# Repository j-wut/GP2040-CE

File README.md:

<p align="center">
  
</p>

<p align="center">
  Multi-Platform Gamepad Firmware for RP2040
</p>

<p align="center">

  <br />

</p>

<p>
  GP2040-CE (Community Edition) is a gamepad firmware for the Raspberry Pi Pico and other boards based on the RP2040 microcontrollers that combines multi-platform compatibility, low latency and a rich feature set to provide endless customization possibilities without sacrificing performance.
</p>

<p>
  GP2040-CE is compatible with PC, PS3, PS4, PS5, Nintendo Switch, Xbox One, Steam Deck, MiSTer and Android.
</p>

## Links

[Downloads](https://gp2040-ce.info/downloads) | [Installation](https://gp2040-ce.info/installation) | [Wiring](https://gp2040-ce.info/controller-build/wiring) | [Usage](https://gp2040-ce.info/usage) | [FAQ](https://gp2040-ce.info/faq/faq-general) | [GitHub](https://github.com/OpenStickCommunity/GP2040-CE)

Full documentation can be found at [https://gp2040-ce.info](https://gp2040-ce.info)

## Features

- Select from 14 input modes including X-Input, Nintendo Switch, Playstation 4/5, Xbox One, D-Input, and Keyboard
- Input latency average of 0.76ms in Xinput and 0.91ms for Playstation 5.
- Multiple SOCD cleaning modes - Up Priority (a.k.a. Stickless), Neutral, and Second Input Priority.
- Left and Right stick emulation via D-pad inputs as well as dedicated toggle switches.
- Dual direction via D-pad + LS/RS.
- Reversed input via a button.
- [Turbo and Turbo LED](https://gp2040-ce.info/add-ons/turbo) with selectable speed
- Per-button RGB LED support.
- PWM Player indicator LED support (XInput only).
- Multiple LED profiles support.
- Support for 128x64 monochrome I2C displays - SSD1306, SH1106, and SH1107 compatible.
- Custom startup splash screen and easy image upload via web configuration.
- Support for passive buzzer speaker (3v or 5v).
- [Built-in, embedded web configuration](https://gp2040-ce.info/web-configurator) - No download required!

Visit the [GP2040-CE Usage](https://gp2040-ce.info/usage) page for more details.

## Performance

Input latency is tested using the methodology outlined at [WydD's inputlag.science website](https://inputlag.science/controller/methodology), using the default 1000 Hz (1 ms) polling rate in the firmware. You can read more about the setup we use to conduct latency testing [HERE](https://github.com/OpenStickCommunity/Site/blob/main/latency_testing/README.md) if you are interested in testing for yourself or would just like to know more about the devices used to do the testing.

| Version | Mode    | Poll Rate | Min     | Max     | Avg     | Stdev   | % on time | %1f skip | %2f skip |
| ------- | ------- | --------- | ------- | ------- | ------- | ------- | --------- | -------- | -------- |
| v0.7.12 | Xinput  | 1 ms      | 0.45 ms | 1.28 ms | 0.76 ms | 0.24 ms | 98.48%    | 1.52%    | 0%       |
| v0.7.12 | Switch  | 1 ms      | 0.41 ms | 1.22 ms | 0.72 ms | 0.24 ms | 98.53%    | 1.47%    | 0%       |
| v0.7.12 | HID USB | 1 ms      | 0.42 ms | 1.25 ms | 0.73 ms | 0.24 ms | 98.52%    | 1.48%    | 0%       |
| v0.7.12 | PS3     | 1 ms      | 0.52 ms | 1.46 ms | 0.83 ms | 0.24 ms | 98.37%    | 1.63%    | 0%       |
| v0.7.12 | PS4     | 1 ms      | 0.55 ms | 2.33 ms | 0.90 ms | 0.32 ms | 98.19%    | 1.81%    | 0%       |
| v0.7.12 | PS5     | 1 ms      | 0.55 ms | 2.38 ms | 0.91 ms | 0.32 ms | 98.18%    | 1.82%    | 0%       |

Full results can be found in the [GP2040-CE v0.7.12 Firmware Latency Test Results](https://github.com/OpenStickCommunity/Site/raw/main/latency_testing/GP2040-CE_Firmware_Latency_Test_Results_v0.7.12.xlsx) .xlsx Sheet.

Results from v0.7.11 can be found [HERE](https://github.com/OpenStickCommunity/Site/raw/main/latency_testing/GP2040-CE_Firmware_Latency_Test_Results_v0.7.11.xlsx). Previous results can be found in the `latency_testing` folder.

### Raspberry Pi 5 / CM5 / Pi 4 / CM4 (Linux USB gadget)

The [`linux/`](linux/README.md) folder has a separate GP2040-CE build that runs on a Raspberry Pi under Linux and acts as a USB controller through the Pi's USB device port. These boards have High Speed USB, so they can ask the host for polling up to 8 kHz. RP2040 and RP2350 boards are Full Speed only and stay at the 1 kHz maximum.

## Support

If you would like to discuss features, issues or anything else related to GP2040-CE please [create an issue](https://github.com/OpenStickCommunity/GP2040-CE/issues/new) or join the [OpenStick GP2040-CE Discord](https://discord.gg/k2pxhke7q8) support channel.

## Contributing

Want to help improve GP2040-CE? There are a bunch of ways to contribute!

### Community Participation

Have an idea for a cool new feature, or just want to discuss some technical details with the developers? Join the [OpenStick GP2040-CE Discord](https://discord.gg/k2pxhke7q8) server to participate in our active and ever-growing community!

### Pull Requests

Pull requests are welcome and encouraged for enhancements, bug fixes and documentation updates.

Please respect the coding style of the file(s) you are working in, and enforce the use of the `.editorconfig` file when present.

## Acknowledgements

- [FeralAI](https://github.com/FeralAI) for building [GP2040](https://github.com/FeralAI/GP2040) and laying the foundation for this community project
- Ha Thach's excellent [TinyUSB library](https://github.com/hathach/tinyusb) examples
- fluffymadness's [tinyusb-xinput](https://github.com/fluffymadness/tinyusb-xinput) sample
- Kevin Boone's [blog post on using RP2040 flash memory as emulated EEPROM](https://kevinboone.me/picoflash.html)
- [bitbank2](https://github.com/bitbank2) for the [OneBitDisplay](https://github.com/bitbank2/OneBitDisplay) and [BitBang_I2C](https://github.com/bitbank2/BitBang_I2C) libraries, which were ported for use with the Pico SDK
- [arntsonl](https://github.com/arntsonl) for the amazing cleanup and feature additions that brought us to v0.5.0
- [alirin222](https://github.com/alirin222) for the awesome turbo code ([@alirin222](https://twitter.com/alirin222) on Twitter)
- [deeebug](https://github.com/deeebug) for improvements to the web-UI and fixing the PS3 home button issue
- [TheTrain](https://github.com/TheTrainGoes/GP2040-Projects) and [Fortinbra](https://github.com/Fortinbra) for helping keep our community chugging along
- [PassingLink](https://github.com/passinglink/passinglink) for the technical details and code for PS4 implementation
- [Youssef Habchi](https://youssef-habchi.com/) for allowing us to purchase a license to use Road Rage font for the project
- [tamanegitaro](https://github.com/tamanegitaro/) and [alirin222](https://github.com/alirin222) for the basis of the mini/classic controller work
- [Ryzee119](https://github.com/Ryzee119) for the wonderful [ogx360_t4](https://github.com/Ryzee119/ogx360_t4/) and xid_driver library for Original Xbox support
- [Santroller](https://github.com/Santroller/Santroller) and [GIMX](https://github.com/matlo/GIMX) for technical examples of Xbox One authentication using pass-through
- [Santroller](https://github.com/Santroller/Santroller) for the code necessary to have Xbox 360 run without a dongle
- [Dycool](https://github.com/Dycool)'s [NS-PC-Control](https://github.com/Dycool/NS-PC-Control) for the technical details on wired Joy-Con, NES and Famicom controller identities
- [PVS-Studio](https://pvs-studio.com/en/pvs-studio/?utm_source=website&utm_medium=github&utm_campaign=open_source) for static code analysis

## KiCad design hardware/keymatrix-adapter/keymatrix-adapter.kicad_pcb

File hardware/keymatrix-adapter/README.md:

# Key matrix diode adapter

A board that turns the 20-pin header of the **RP2040 Advanced Breakout Board (USB Passthrough edition)** into 44
matrix switch inputs with full N-key rollover: all 15 button pins as 4 rows x 11 columns. It goes with the
[RP2040AdvancedBreakoutBoardUSBPassthroughMatrix](../../configs/RP2040AdvancedBreakoutBoardUSBPassthroughMatrix)
firmware config.

- 156 x 112 mm, 2 layers, all through-hole connectors plus 44 SOD-123 diodes.
- **J1** connects to the breakout board's 20-pin header with a straight 20-pin IDC ribbon cable (pin 1 to pin 1).
- **J2-J5** are two pairs of 20-pin switch connectors (A and B).
- **J6-J14** are screw terminals: two per switch, in the same order as the connector pins. The last 4 switches
  are on screw terminals only.
- One 1N4148W diode per switch, already on the board. No diodes are needed in the wiring.

## How a switch is wired

Every switch has a **slot** with two contacts, A and B. Wire the switch between them, either on the connector pair
(pin N on A and pin N on B) or on its two neighbouring screw terminals. Both reach the same switch. A switch has no
polarity, so either wire can go to A.

- **A** goes through the switch's diode to its row.
- **B** is its column. All the B contacts of one column are connected on the board, so a harness can share them.
  A contacts must never be shared.

Do not plug a normal 20-pin button harness (buttons wired to ground) into the switch connectors.

## Slot order

Both pairs have the same order. **Pair 1 follows the breakout's 20-pin header.** Each of its 15 button pins
carries the switch that defaults to that pin's button, so a harness made for the breakout's pinout lines up:

- Pin 16 is K4 (L2), pin 8 is P1 (B3), pin 1 is U (Up), and so on.

The breakout's 5 power and ground positions (pins 12 and 17-20) carry five more switches. Pair 2 carries the next
20 in row order, and the last 4 are on screw terminals only. R*n*C*m* is the switch in row *n*, column *m*, as listed in the web config (Add-ons > Keyboard
Matrix).

| Pin | Pair 1 (J2 A / J3 B) | Pair 2 (J4 A / J5 B) |
|-----|-----|-----|
| 1 | U (R2C4) | R2C10 |
| 2 | D (R2C3) | R2C11 |
| 3 | R (R2C2) | R3C1 |
| 4 | L (R2C1) | R3C2 |
| 5 | S1 (R1C11) | R3C3 |
| 6 | A1 (R1C10) | R3C4 |
| 7 | S2 (R1C9) | R3C5 |
| 8 | P1 (R1C8) | R3C6 |
| 9 | P2 (R1C7) | R3C7 |
| 10 | P3 (R1C6) | R3C8 |
| 11 | P4 (R1C5) | R3C9 |
| 12 | R2C5 | R3C10 |
| 13 | K1 (R1C4) | R3C11 |
| 14 | K2 (R1C3) | R4C1 |
| 15 | K3 (R1C2) | R4C2 |
| 16 | K4 (R1C1) | R4C3 |
| 17 | R2C6 | R4C4 |
| 18 | R2C7 | R4C5 |
| 19 | R2C8 | R4C6 |
| 20 | R2C9 | R4C7 |

Screw terminals only: R4C8, R4C9, R4C10, R4C11.

The screw terminals hold the same slots in the same order, A then B:

- pair 1 along the top edge, left to right
- pair 2 along the bottom edge, left to right
- the terminal-only switches down the left edge

Each slot is labelled on the silkscreen.

GPIO 20-22 (A2, L3, R3 on the breakout's 4-pin harness) are not on the 20-pin header and stay ordinary buttons on
the breakout board. Don't wire anything else to the breakout's own K1-K4, P1-P4, S1, S2, A1, L, R, D, U terminals
while the adapter is connected: those GPIOs are matrix lines now.

## Signals

| J1 pin | Signal | Breakout label | | J1 pin | Signal | Breakout label |
|-----|--------|----|-|-----|--------|----|
| 1   | ROW4 (GP19) | U  | | 2   | ROW3 (GP18) | D |
| 3   | ROW2 (GP17) | R  | | 4   | ROW1 (GP16) | L |
| 5   | COL11 (GP15) | S1 | | 6   | COL10 (GP14) | A1 |
| 7   | COL9 (GP13) | S2 | | 8   | COL8 (GP12) | P1 |
| 9   | COL7 (GP11) | P2 | | 10  | COL6 (GP10) | P3 |
| 11  | COL5 (GP9)  | P4 | | 12  | GND | G |
| 13  | COL4 (GP8)  | K1 | | 14  | COL3 (GP7) | K2 |
| 15  | COL2 (GP6)  | K3 | | 16  | COL1 (GP5) | K4 |
| 17  | GND | G | | 18  | GND | G |
| 19  | +5V | VCC | | 20  | +5V | VCC |

The pin numbers follow the breakout board's pinout image (pin 1 next to the "U" label, pins 19 and 20 are +5 V).
Check pin 1 on your board before the first power-up.

## Files

| File | What it is |
|------|------------|
| `keymatrix-adapter.kicad_sch`, `.kicad_pcb`, `.kicad_pro` | KiCad 7 project |
| `fab/gerbers/` | Gerbers and drill file for ordering the PCB |
| `fab/keymatrix-adapter-bom.csv` | Bill of materials |
| `fab/keymatrix-adapter-pos.csv` | Pick-and-place positions for the diodes |
| `fab/keymatrix-adapter-schematic.pdf` | Schematic |
| `generate.py`, `autoroute.py` | Build the schematic and the routed PCB from one parts and nets table |
| `check.py` | Runs the checks below and writes `fab/` |
| `simulate.py`, `sim-results.txt` | ngspice simulation of the full matrix through this board, and its results |

## Checks

`python3 generate.py && python3 check.py` (needs KiCad 7 with its Python module) regenerates the design and checks:

- KiCad DRC: no clearance or other violations, no unconnected pads.
- The schematic netlist (from `kicad-cli`) connects exactly the same pads as the PCB.
- Every one of the 44 switches has its own diode, cathode on the right row, and the rows and columns match
  `KEY_MATRIX_ROW_PINS` / `KEY_MATRIX_COL_PINS` in the board config.
- Every switch is on exactly one connector slot. Pair 1 is in breakout pin order. The screw terminals, read around
  the board, are in the same slot order as the connectors.

## Simulation

`python3 simulate.py` runs ngspice on the whole 4 x 11 matrix through this board: RP2040 pull-ups and pins, the ribbon
cable, the copper of every net on this PCB (measured from the board file), the 44 diodes, and the harness wiring
(each switch's own wire plus the column's B wire daisy-chained through its four switches). It scans the way the firmware
does and checks every read for several held-switch patterns, including all 44 held. Results:
[sim-results.txt](sim-results.txt).

| Wiring (ribbon / switch wire / column chain) | Press seen at the pin | Column recovery | Result with defaults |
|-----|-----|-----|-----|
| short: 0.15 m / 0.2 m / 1 m | 0.2 us | up to 11 us | pass |
| typical arcade stick: 0.3 m / 0.5 m / 3 m | 0.4 us | up to 20 us | pass |
| long cabinet: 1 m / 1 m / 6 m | 0.6 us | up to 35 us | pass |

Wire length adds no meaningful latency: a press shows up at the pin in under 0.6 us even with cabinet
wiring. What wiring does set is how long a released row's columns take to climb back through the RP2040's weak
pull-ups. The firmware waits a fixed **row delay** after each row for that (default 50 us, set in the web config
next to the settle time). With the defaults a full scan of all four rows takes about 224 us, well inside the 1 ms
between USB reports. Shorter wiring can use a smaller row delay; see the table in
[docs/keymatrix-sim/results.txt](../../docs/keymatrix-sim/results.txt).

Not built or tested on hardware yet.

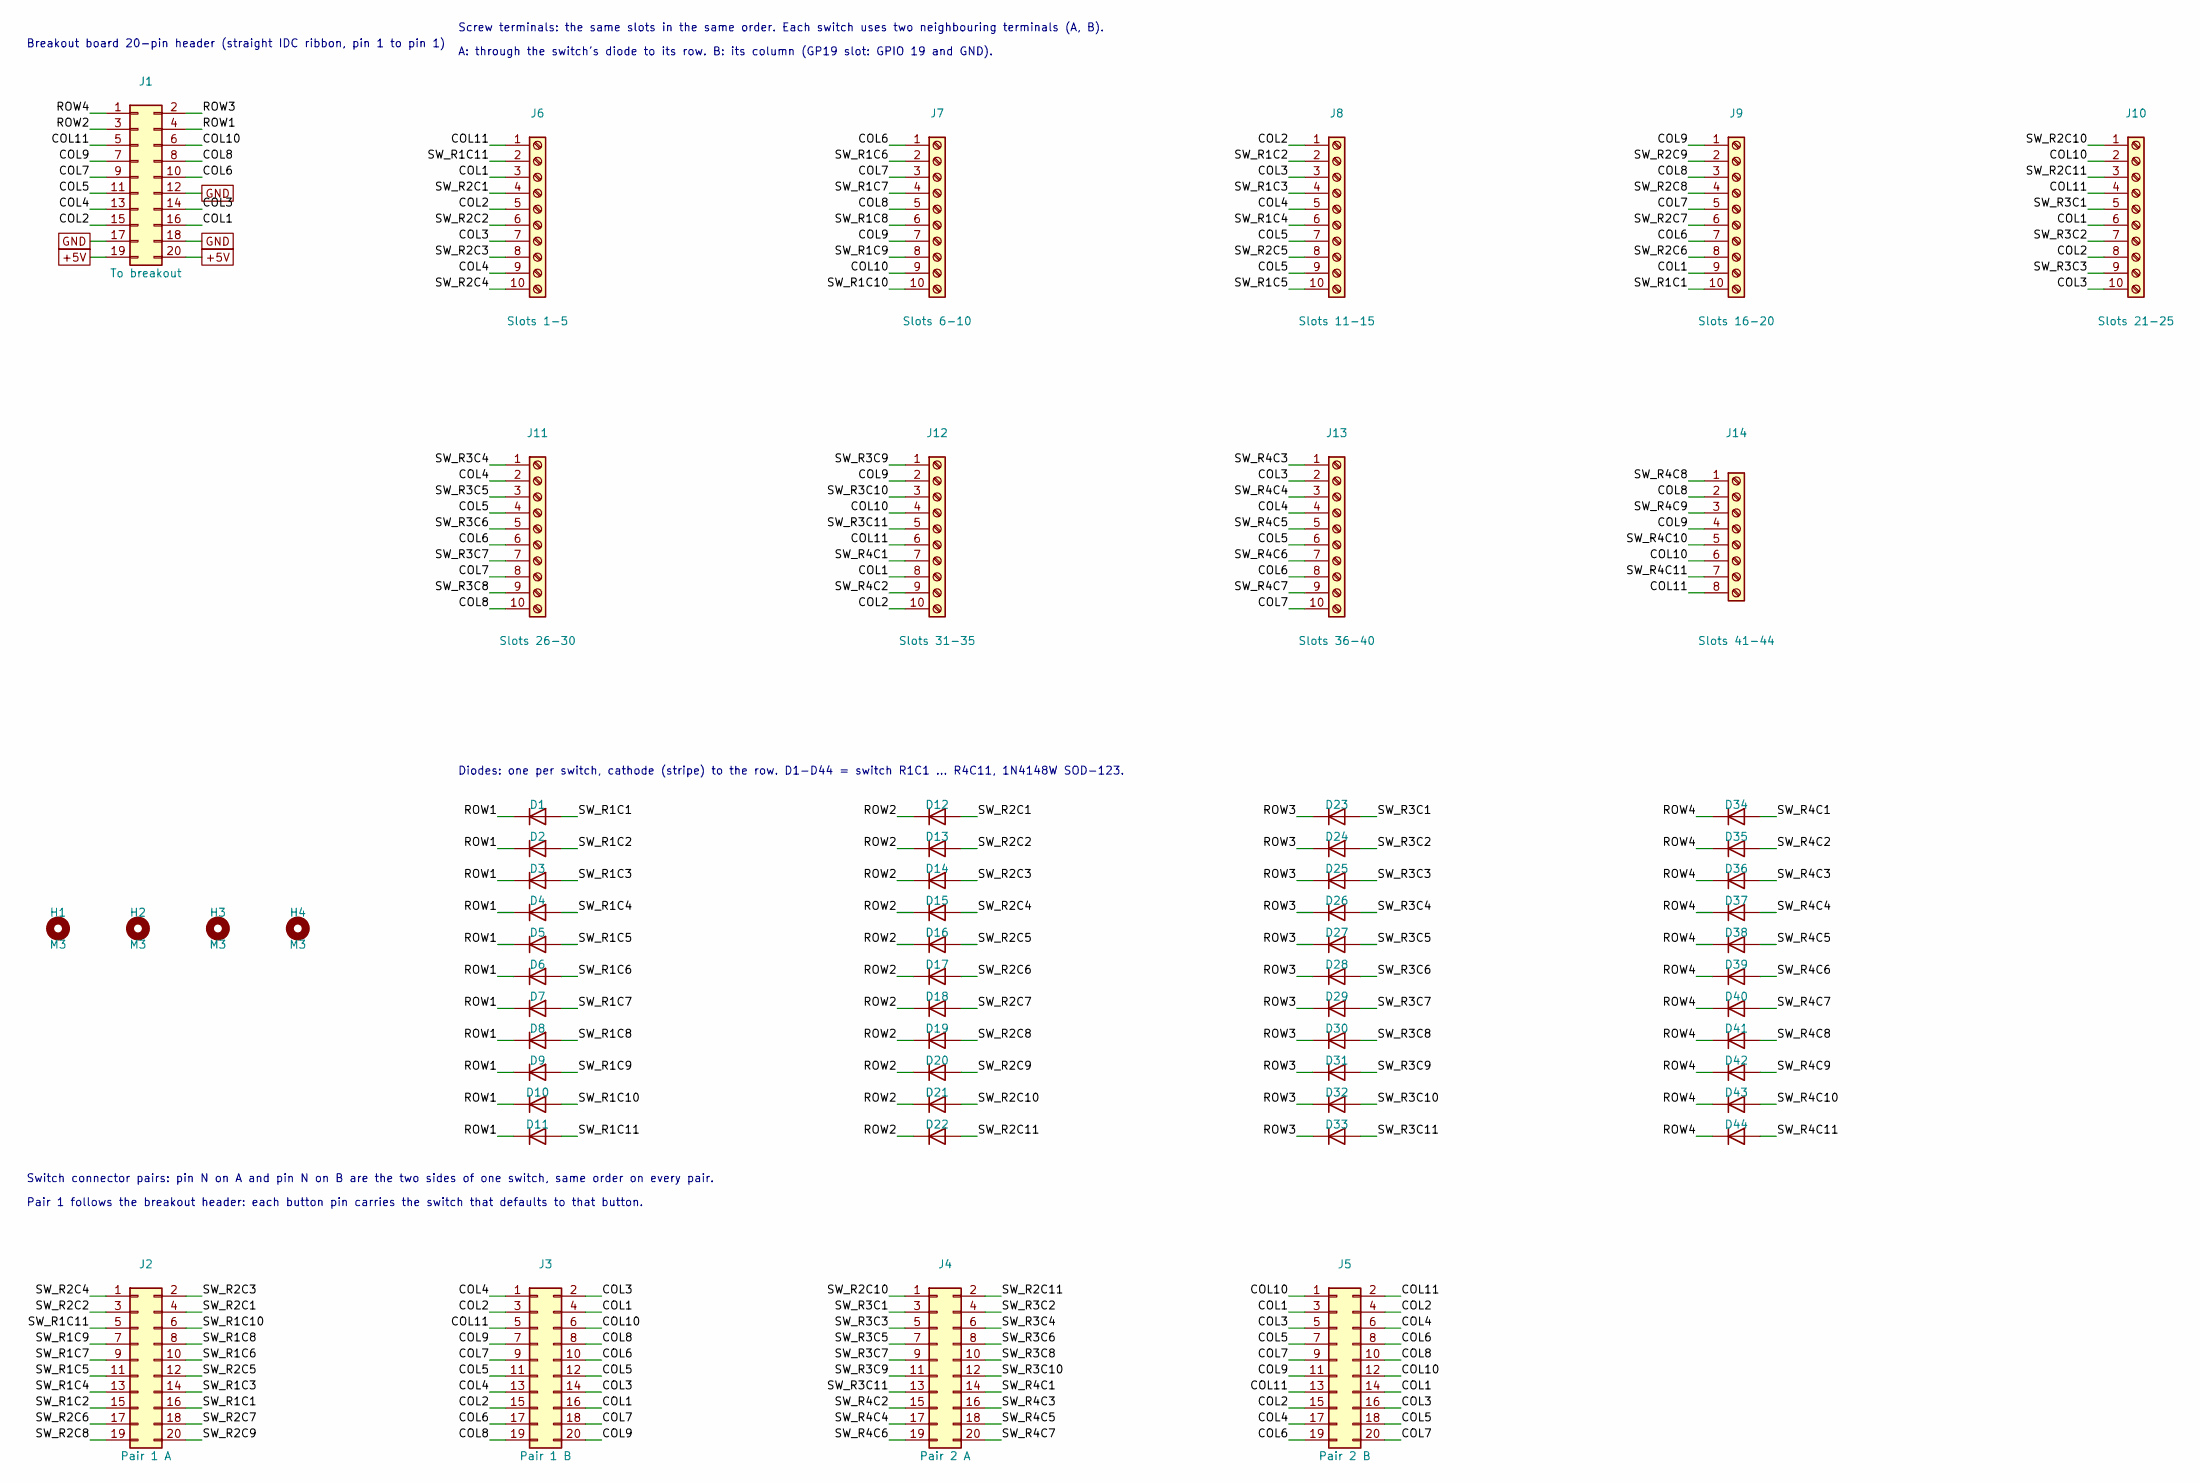
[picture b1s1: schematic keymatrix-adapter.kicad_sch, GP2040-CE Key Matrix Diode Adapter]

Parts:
D1, D2, D3, D4, D5, D6, D7, D8, D9, D10, D11, D12, D13, D14, D15, D16, D17, D18, D19, D20, D21, D22, D23, D24, D25, D26, D27, D28, D29, D30, D31, D32, D33, D34, D35, D36, D37, D38, D39, D40, D41, D42, D43, D44: 1N4148W; D_SOD-123
H1, H2, H3, H4: M3; MountingHole_3.2mm_M3
J1: To breakout; IDC-Header_2x10_P2.54mm_Vertical
J2: Pair 1 A; IDC-Header_2x10_P2.54mm_Vertical
J3: Pair 1 B; IDC-Header_2x10_P2.54mm_Vertical
J4: Pair 2 A; IDC-Header_2x10_P2.54mm_Vertical
J5: Pair 2 B; IDC-Header_2x10_P2.54mm_Vertical
J6: Slots 1-5; TerminalBlock_Phoenix_PT-1,5-10-3.5-H_1x10_P3.50mm_Horizont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
J7: Slots 6-10; TerminalBlock_Phoenix_PT-1,5-10-3.5-H_1x10_P3.50mm_Horizont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
J8: Slots 11-15; TerminalBlock_Phoenix_PT-1,5-10-3.5-H_1x10_P3.50mm_Horizont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
J9: Slots 16-20; TerminalBlock_Phoenix_PT-1,5-10-3.5-H_1x10_P3.50mm_Horizont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
J10: Slots 21-25; TerminalBlock_Phoenix_PT-1,5-10-3.5-H_1x10_P3.50mm_Horizont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
J11: Slots 26-30; TerminalBlock_Phoenix_PT-1,5-10-3.5-H_1x10_P3.50mm_Horizont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
J12: Slots 31-35; TerminalBlock_Phoenix_PT-1,5-10-3.5-H_1x10_P3.50mm_Horizont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
J13: Slots 36-40; TerminalBlock_Phoenix_PT-1,5-10-3.5-H_1x10_P3.50mm_Horizont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
J14: Slots 41-44; TerminalBlock_Phoenix_PT-1,5-8-3.5-H_1x08_P3.50mm_Horizontal

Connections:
+5V: J1.19, J1.20
COL1: J1.16, J3.4, J3.16, J5.3, J5.14, J6.3, J9.9, J10.6, J12.8
COL2: J1.15, J3.3, J3.15, J5.4, J5.15, J6.5, J8.1, J10.8, J12.10
COL3: J1.14, J3.2, J3.14, J5.5, J5.16, J6.7, J8.3, J10.10, J13.2
COL4: J1.13, J3.1, J3.13, J5.6, J5.17, J6.9, J8.5, J11.2, J13.4
COL5: J1.11, J3.11, J3.12, J5.7, J5.18, J8.7, J8.9, J11.4, J13.6
COL6: J1.10, J3.10, J3.17, J5.8, J5.19, J7.1, J9.7, J11.6, J13.8
COL7: J1.9, J3.9, J3.18, J5.9, J5.20, J7.3, J9.5, J11.8, J13.10
COL8: J1.8, J3.8, J3.19, J5.10, J7.5, J9.3, J11.10, J14.2
COL9: J1.7, J3.7, J3.20, J5.11, J7.7, J9.1, J12.2, J14.4
COL10: J1.6, J3.6, J5.1, J5.12, J7.9, J10.2, J12.4, J14.6
COL11: J1.5, J3.5, J5.2, J5.13, J6.1, J10.4, J12.6, J14.8
GND: J1.12, J1.17, J1.18
ROW1: D1.1 (K), D2.1 (K), D3.1 (K), D4.1 (K), D5.1 (K), D6.1 (K), D7.1 (K), D8.1 (K), D9.1 (K), D10.1 (K), D11.1 (K), J1.4
ROW2: D12.1 (K), D13.1 (K), D14.1 (K), D15.1 (K), D16.1 (K), D17.1 (K), D18.1 (K), D19.1 (K), D20.1 (K), D21.1 (K), D22.1 (K), J1.3
ROW3: D23.1 (K), D24.1 (K), D25.1 (K), D26.1 (K), D27.1 (K), D28.1 (K), D29.1 (K), D30.1 (K), D31.1 (K), D32.1 (K), D33.1 (K), J1.2
ROW4: D34.1 (K), D35.1 (K), D36.1 (K), D37.1 (K), D38.1 (K), D39.1 (K), D40.1 (K), D41.1 (K), D42.1 (K), D43.1 (K), D44.1 (K), J1.1
SW_R1C1: D1.2 (A), J2.16, J9.10
SW_R1C2: D2.2 (A), J2.15, J8.2
SW_R1C3: D3.2 (A), J2.14, J8.4
SW_R1C4: D4.2 (A), J2.13, J8.6
SW_R1C5: D5.2 (A), J2.11, J8.10
SW_R1C6: D6.2 (A), J2.10, J7.2
SW_R1C7: D7.2 (A), J2.9, J7.4
SW_R1C8: D8.2 (A), J2.8, J7.6
SW_R1C9: D9.2 (A), J2.7, J7.8
SW_R1C10: D10.2 (A), J2.6, J7.10
SW_R1C11: D11.2 (A), J2.5, J6.2
SW_R2C1: D12.2 (A), J2.4, J6.4
SW_R2C2: D13.2 (A), J2.3, J6.6
SW_R2C3: D14.2 (A), J2.2, J6.8
SW_R2C4: D15.2 (A), J2.1, J6.10
SW_R2C5: D16.2 (A), J2.12, J8.8
SW_R2C6: D17.2 (A), J2.17, J9.8
SW_R2C7: D18.2 (A), J2.18, J9.6
SW_R2C8: D19.2 (A), J2.19, J9.4
SW_R2C9: D20.2 (A), J2.20, J9.2
SW_R2C10: D21.2 (A), J4.1, J10.1
SW_R2C11: D22.2 (A), J4.2, J10.3
SW_R3C1: D23.2 (A), J4.3, J10.5
SW_R3C2: D24.2 (A), J4.4, J10.7
SW_R3C3: D25.2 (A), J4.5, J10.9
SW_R3C4: D26.2 (A), J4.6, J11.1
SW_R3C5: D27.2 (A), J4.7, J11.3
SW_R3C6: D28.2 (A), J4.8, J11.5
SW_R3C7: D29.2 (A), J4.9, J11.7
SW_R3C8: D30.2 (A), J4.10, J11.9
SW_R3C9: D31.2 (A), J4.11, J12.1
SW_R3C10: D32.2 (A), J4.12, J12.3
SW_R3C11: D33.2 (A), J4.13, J12.5
SW_R4C1: D34.2 (A), J4.14, J12.7
SW_R4C2: D35.2 (A), J4.15, J12.9
SW_R4C3: D36.2 (A), J4.16, J13.1
SW_R4C4: D37.2 (A), J4.17, J13.3
SW_R4C5: D38.2 (A), J4.18, J13.5
SW_R4C6: D39.2 (A), J4.19, J13.7
SW_R4C7: D40.2 (A), J4.20, J13.9
SW_R4C8: D41.2 (A), J14.1
SW_R4C9: D42.2 (A), J14.3
SW_R4C10: D43.2 (A), J14.5
SW_R4C11: D44.2 (A), J14.7

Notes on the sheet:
Breakout board 20-pin header (straight IDC ribbon, pin 1 to pin 1)
Switch connector pairs: pin N on A and pin N on B are the two sides of one switch, same order on every pair.
Pair 1 follows the breakout header: each button pin carries the switch that defaults to that button.
Screw terminals: the same slots in the same order. Each switch uses two neighbouring terminals (A, B).
A: through the switch's diode to its row. B: its column (GP19 slot: GPIO 19 and GND).
Diodes: one per switch, cathode (stripe) to the row. D1-D44 = switch R1C1 ... R4C11, 1N4148W SOD-123.

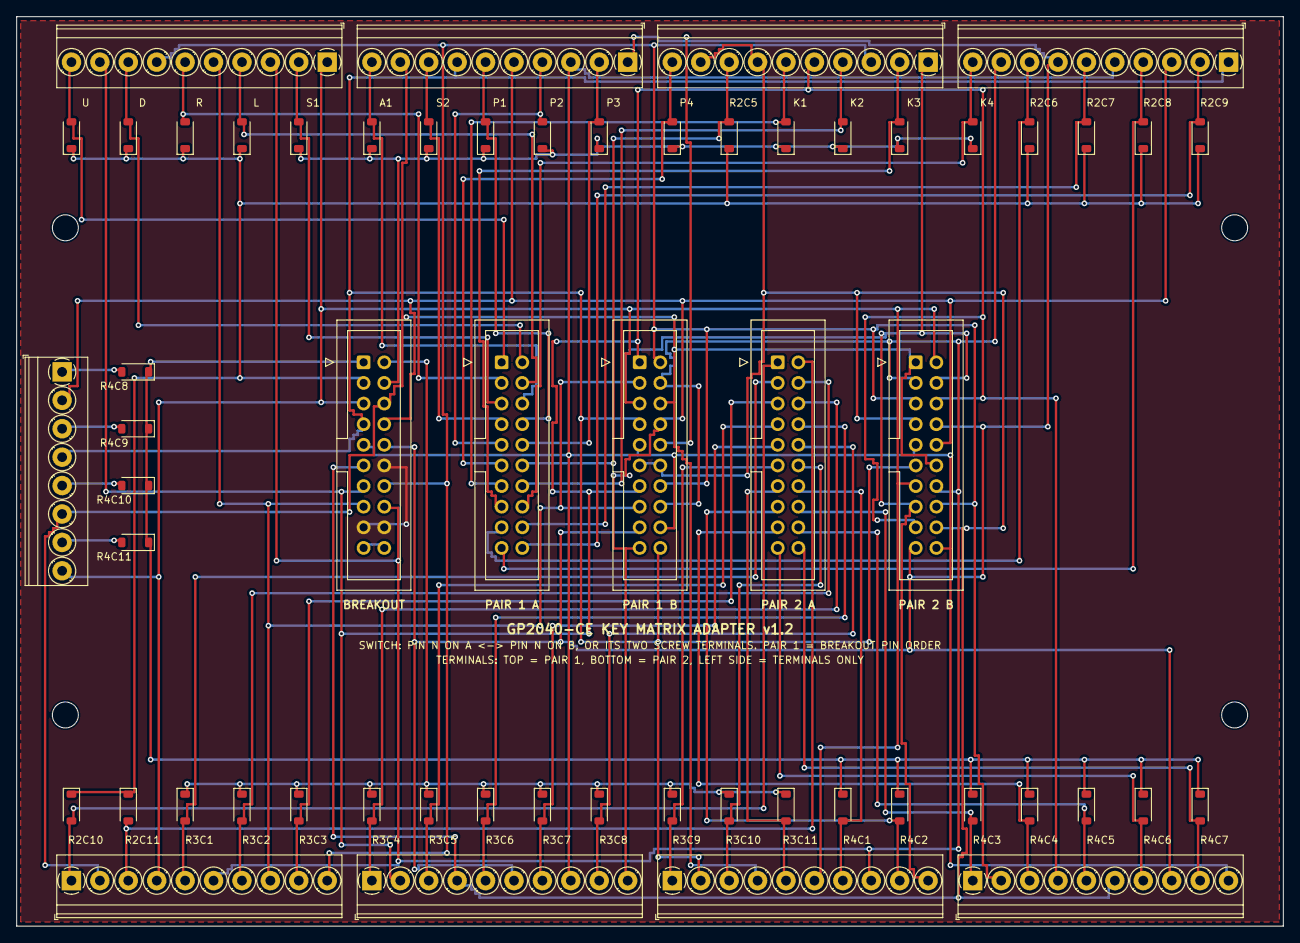
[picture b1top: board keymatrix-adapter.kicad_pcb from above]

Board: 2 copper layers, 156.0 x 112.0 mm, 62 parts (0 on the bottom side), 61 nets.

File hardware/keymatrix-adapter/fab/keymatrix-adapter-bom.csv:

Qty,References,Value,Footprint,Description
5,J1 J2 J3 J4 J5,2x10 box header,Connector_IDC:IDC-Header_2x10_P2.54mm_Vertical,"2.54 mm shrouded IDC box header, vertical, through-hole"
8,J6 J7 J8 J9 J10 J11 J12 J13,10-way terminal,"TerminalBlock_Phoenix:TerminalBlock_Phoenix_PT-1,5-10-3.5-H_1x10_P3.50mm_Horizontal","3.5 mm pitch screw terminal, Phoenix PT 1,5/10-3,5-H or equivalent"
1,J14,8-way terminal,"TerminalBlock_Phoenix:TerminalBlock_Phoenix_PT-1,5-8-3.5-H_1x08_P3.50mm_Horizontal","3.5 mm pitch screw terminal, Phoenix PT 1,5/8-3,5-H or equivalent"
44,D1 D2 D3 D4 D5 D6 D7 D8 D9 D10 D11 D12 D13 D14 D15 D16 D17 D18 D19 D20 D21 D22 D23 D24 D25 D26 D27 D28 D29 D30 D31 D32 D33 D34 D35 D36 D37 D38 D39 D40 D41 D42 D43 D44,1N4148W,Diode_SMD:D_SOD-123,"Small-signal switching diode, SOD-123"

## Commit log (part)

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2024-03-25 fix issue where setPinMappingsV2 was actually ignoring input
2024-03-25 fix usage of button masks for hotkeys
    I probably introduced this in a bad rebase
2024-03-25 implement get/setPinMappingsV2 which includes the new masks
2024-03-25 multi mapping page (#7)
    * remove double initialization of gamepad GPIOs
    * have getProfilePinMappings return whole GpioMappingInfos
    before it returned just the actions, which was fine, but now we're
    adding more stuff to the infos, so return the whole struct rather than
    just the GpioAction within it
    * define a custom button combo to a GPIO pin
2024-03-25 add a disclaimer about multi mapping only working on Profile 1
2024-03-25 have getProfilePinMappings return whole GpioMappingInfos
    before it returned just the actions, which was fine, but now we're
    adding more stuff to the infos, so return the whole struct rather than
    just the GpioAction within it
2024-03-25 define a custom button combo to a GPIO pin
    this expands GpioMappingInfo to include dpad and button masks and uses
    those masks when setting up the button maps in Gamepad. this allows for
    a GPIO pin to trigger any arbitrary set of buttons
2024-11-14 simplify lever display logic for digital, fix a bug
2024-11-15 adjust buttonCount logic to allow for offsets between buttons
2024-11-17 allow arbitrary button index for LEDs
2026-02-17 readding GP_ELEMENT_PIN_BUTTON, previously only grepped buttonlayouts.h
2026-02-17 GPButton display improvements
    1) Delete All the pin mapping logic, imo: GPButton (GamePadButton) should map
    to a button state. Existing code was displaying pin state instead.
    - If pin state graphics are wanted, that should be put in a
    different ui element, not the Button.
    2) Directly use buttonState for determining if button is pressed or not.
2026-02-17 process addons in config mode, use processed gamepad state for config ui navigation
2026-03-21 adding options for mux, take the channel selecting logic from he_triggers
2026-03-21 renaming properties, adding basic selectors in analog add-on
2026-03-22 getAddon needs to return options for it to allow updates
2026-03-27 adding linearity, and angle snapping
2026-03-28 refactoring the joystick calibration, using new endpoint
2026-03-28 analog specific endpoints
2026-03-28 json response issue
2026-03-29 final fix angle snapping, and linearity
2026-03-29 analog rotational offset
2026-03-29 merged improvement/processed_config_nav@ac0a65d0b2008c7bca06f3dd52404cc1c9c0a818
2026-03-29 merged cleanup/display_gpbutton@f84d18f3d1c6d24a0d827d733d2b8857d1d5961c
2026-03-29 increase ADC read speed
2026-03-29 fix direction snapping persistance
2026-03-29 begin working on refactoring/updates to configuration ui
2026-03-30 fix angle rotation offset... math functions expect counter clockwise
2026-04-01 initial calibration ui modal, split plate splines visualization
2026-04-03 BIG analog refactor in progress
2026-04-03 significant settings refactor... -> going to make this a brand new plugin instead of tacking onto existing
2026-04-04 fix old calibration for dev
2026-04-05 begin work on analog_plus
2026-04-07 refactor complete, todo: cleanup for build
2026-04-07 fix build errors
2026-04-07 default configs for analog plus, last step, web api
2026-04-07 full revert analog to main, all new features will be in AnalogPlus
2026-04-07 finalize?, todo: testing and translations
2026-04-07 remove things from refactor
2026-04-07 fix urls
2026-04-07 fix select_pins
2026-04-07 add AnalogPlus to setup
2026-04-07 fix build
2026-04-09 fix ema bug... testing, ui angle snapping
2026-05-05 fix analog snapping variable name
